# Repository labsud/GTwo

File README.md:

<h1 id="gtwo_shield_for_arduino_due_tinyg_2">GTwo Shield for Arduino DUE &amp; TinyG 2</h1>

<p><a href="https://github.com/synthetos/TinyG">TinyG</a> is a 6 axis motion control system designed by Synthetos for driving CNC, Laser cutters, ans so on. It have been designed to run on Atmel ATxmega192. It&#8217;s a complete system (hard + soft).</p>

<p>Some faeatures : </p>

<ul>
<li>6 axis motion (XYZABC axes)</li>
<li>jerk controlled motion for acceleration planning (3rd order motion planning)</li>
<li>status displays (&#8216;?&#8217; character)</li>
<li>XON/XOFF and RTS/CTS protocol over USB serial</li>
<li>RESTful interface using JSON</li>
</ul>

<p><a href="https://github.com/synthetos/g2">TinyG 2</a> is a TinyG ARM port, also developed by Synthetos, working on Atmel Arm Processors, like the one used on low cost Arduino DUE. That port can be configured for using GRBL shields (Arduino Uno form factor) but unfortunately, pinout is slightly differents, so there&#8217;s no way to have more than 3 motors running. No commands, no emergency stops, spindle or homing&#8230; </p>

<p>GTwo is a shield designed to allow easy use or the port of TinyG with all functionnalities. </p>

<p>That shield can be used :</p>

<ul>
<li>Directly connected to a <a href="https://www.google.fr/search?q=tb6560+red&amp;num=20&amp;safe=off&amp;source=lnms&amp;tbm=isch&amp;sa=X&amp;ved=0ahUKEwinnOrSrarKAhXkpnIKHYe3DXwQ_AUIBygB&amp;biw=917&amp;bih=418">TB 6560 &#8220;Red&#8221;</a>, for a maximum of 4 axis (X,Y,Z,A) and 4 GPIO inputs (I.E. homing X,Y,Z and emergency stop)</li>
<li>Connected thru 6 X 6 pins connectors to discrete drivers like Leadshine, Gekko, etc., allowing up to 6 axis (X,Y,Z,A,B,C).</li>
</ul>

<h4 id="caracteristics">Caracteristics</h4>

<ul>
<li>Mostly passive shield, with all connectors for connecting spindle, PWM Spindle, coolant, homing &amp; Limits, switch for program control, up to 6 axis stepper driver boards</li>
<li>Since DUE is not 5V tolerant, limits inputs are level translated to be used @5V</li>
<li>All other inouts ARE not, and should no be connected to anything else than a 0V. (program control)</li>
</ul>

<h4 id="connections">Connections</h4>

<h5 id="when_using_a_tb6560_power_board_">When using a TB6560 power board :</h5>

That work is the property of Jean-Philippe Civade (jp at civade dot com) and is shared under <a href="licence-CC-By-NC 3.0.txt">Creative Common NonCommercial 3.0</a>

<ul>
<li>JP1 : For connectig to a TB6560 &#8220;Red&#8221; Stepper driver board. A cable must be made with a HE10-26F > DB25F emulating parallel port. If using JP1, don&#8217;t use M1>M6</li>
<li>JP2 : Limits configuration for TB6560. Must be left unequipped if using M1 > M6 connections.</li>
<li>JP4 : Relay config. Must be left unequipped if using M1 > M6 connections.</li>
</ul>

<h5 id="when_using_m1_m6_connections_to_discrete_drivers">When using M1 > M6 connections to discrete drivers</h5>

<ul>
<li>M1 > M6 : Allows to connect up to 6 steppers motors (X/Y/Z/A/B/C). If using M1>M6, don&#8217;t use JP1.</li>
<li>JP3 : Limits inputs. Allow to connect limit and/or homing switches (X-, X+, Y-, Y+, Z-, Z+), emergency stop and optionnaly Hardware interlock. All inputs are 5V tolerant.</li>
<li>JP6 : Stepper power conf </li>
</ul>

<p>M1 to M6 pinout :
* Broche 1 : Step
* Broche 2 : Dir
* Broche 3 : Enable motor (independant enable for each axis)
* Broche 4 : GND
* Broche 5 : Global Enable for all axis
* Broche 6 : VCC (3.3V or 5V depending of JP6) setting</p>

<h5 id="other_connectors_">Other connectors :</h5>

<ul>
<li>JP5 : Spindle &amp; Coolant outputs (3.3V). &#8220;Spindle&#8221; is for Spindle on/off, &#8220;dir&#8221; is for spindle direction (CW/CCW), &#8220;PWM&#8221; is for connecting a PWM spindle, &#8220;PW2&#8221; is an optionnal secondary PWM, &#8220;Cool&#8221; is for connecting cooolant command. </li>
<li>JP7 : Control inputs. Connect swtches for Soft Reset (SR), Feed Hold (Hold), Cycle Start (Run), Emergency Stop (ESTP) or hardware reset (RST)</li>
</ul>

<h5 id="configuration_jumpers_">Configuration Jumpers :</h5>

<p>JP2 : Must be equipped with 4 jumpers allowing to route X- or X+ to Pin 10 of parallel port, Y- or Y+ to pin 11 of parallel port, Z-or Z+ on pin 12 of paralel port, and emergency stop or hardware interlock on pin 13 of parallel port. 
JP4 : Must be equipped with 1 jumper allowing to route motor or coolant to the embedded relay of TB6560 red board.
JP6 : Must be equipped with 1 jumper to route a 3.3V or a 5V to M1 > M6 pin 6.</p>

<h5 id="associated_documents_">Associated Documents :</h5>

<ul>
<li><a href="GTwoShieldSchematics.pdf">Schematics</a></li>
<li><a href="partlist.txt">BOM</a></li>
<li><a href="GTwoShield.zip">ZIP archive for manufacturing</a></li>
<li><a href="imgs/DUE tinyG2 pinout 0.2.pdf">Due Pinout for Tiny G2</a></li>
<li><a href="imgs/GTwoShieldAssembly.pdf">Assembly</a></li>
<li><a href="imgs/GTwoShieldTop.png">Top view</a></li>
<li><a href="imgs/GTwoShieldBottom.png">Bottom view</a></li>
</ul>

<h5 id="example_configuration_">Example configuration :</h5>

<p>This configuration fits to a machine with origin switches at the bottom left ad top Z, for a CNC machine. GTtwo is connected to a TB6560 driver board, and board relay is used to power the spindle. (motor = M3/M5 Gcode). 
TB6560 inputs are Xmin, Ymin, ZMax, Emergency stop. A 3.3V is routed to M1>M6 pin 6.</p>

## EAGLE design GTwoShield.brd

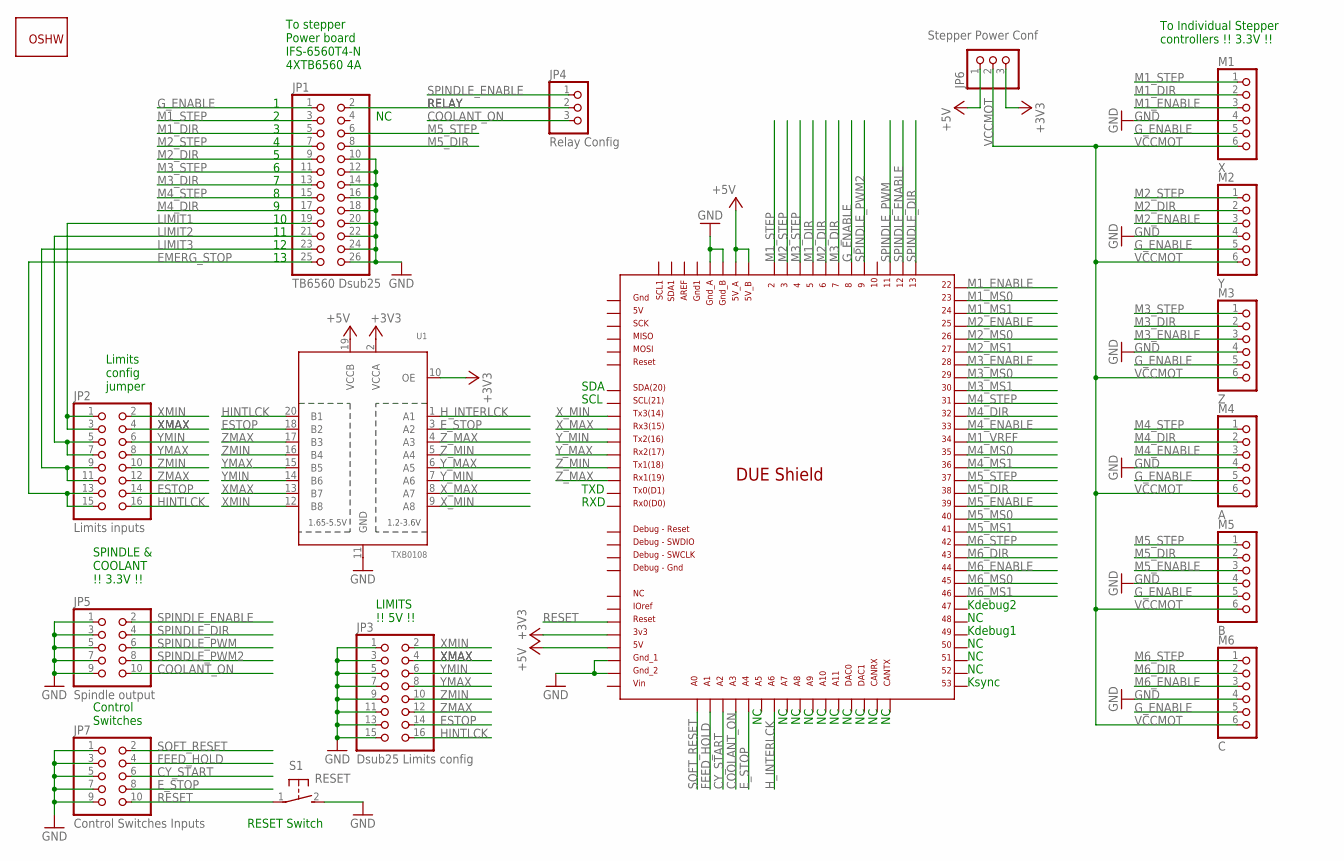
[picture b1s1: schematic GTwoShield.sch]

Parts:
GOLD_ORB_SM1: OSHWLOGO_GOLD_ORB_MED; OSHW1
JP1: TB6560 Dsub25; 2X13
JP2: Limits inputs; 2X08
JP3: Dsub25 Limits config; 2X08
JP4: Relay Config; 1X03
JP5: Spindle output; 2X05
JP6: Stepper Power Conf; 1X03
JP7: Control Switches Inputs; 2X05
M1: X; 1X06
M2: Y; 1X06
M3: Z; 1X06
M4: A; 1X06
M5: B; 1X06
M6: C; 1X06
S1: RESET; B3F-31XX
U1: TXB0108; TSSOP20
U$1: DUE(NORMAL)

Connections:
+3V3: JP6.3, U1.2 (VCCA), U1.10 (OE), U$1.3V3
+5V: JP6.1, U1.19 (VCCB), U$1.5V, U$1.5V_A, U$1.5V_B
COOLANT_ON: JP4.3, JP5.10, U$1.A3
CY_START: JP7.6, U$1.A2
EMERG_STOP: JP1.25, JP2.13, JP2.15
ESTOP: JP2.14, JP3.14, U1.18 (B2)
E_STOP: JP7.8, U1.3 (A2), U$1.A4
FEED_HOLD: JP7.4, U$1.A1
GND: JP1.10, JP1.12, JP1.14, JP1.16, JP1.18, JP1.20, JP1.22, JP1.24, JP1.26, JP3.1, JP3.3, JP3.5, JP3.7, JP3.9, JP3.11, JP3.13, JP3.15, JP5.1, JP5.3, JP5.5, JP5.7, JP5.9, JP7.1, JP7.3, JP7.5, JP7.7, JP7.9, M1.4, M2.4, M3.4, M4.4, M5.4, M6.4, S1.2 (S), U1.11 (GND), U$1.GND_1, U$1.GND_2, U$1.GND_A, U$1.GND_B
G_ENABLE: JP1.1, M1.5, M2.5, M3.5, M4.5, M5.5, M6.5, U$1.8
HINTLCK: JP2.16, JP3.16, U1.20 (B1)
H_INTERLCK: U1.1 (A1), U$1.A6
LIMIT1: JP1.19, JP2.1, JP2.3
LIMIT2: JP1.21, JP2.5, JP2.7
LIMIT3: JP1.23, JP2.9, JP2.11
M1_DIR: JP1.5, M1.2, U$1.5
M1_ENABLE: M1.3, U$1.22
M1_MS0: U$1.23
M1_MS1: U$1.24
M1_STEP: JP1.3, M1.1, U$1.2
M1_VREF: U$1.34
M2_DIR: JP1.9, M2.2, U$1.6
M2_ENABLE: M2.3, U$1.25
M2_MS0: U$1.26
M2_MS1: U$1.27
M2_STEP: JP1.7, M2.1, U$1.3
M3_DIR: JP1.13, M3.2, U$1.7
M3_ENABLE: M3.3, U$1.28
M3_MS0: U$1.29
M3_MS1: U$1.30
M3_STEP: JP1.11, M3.1, U$1.4
M4_DIR: JP1.17, M4.2, U$1.32
M4_ENABLE: M4.3, U$1.33
M4_MS0: U$1.35
M4_MS1: U$1.36
M4_STEP: JP1.15, M4.1, U$1.31
M5_DIR: JP1.8, M5.2, U$1.38
M5_ENABLE: M5.3, U$1.39
M5_MS0: U$1.40
M5_MS1: U$1.41
M5_STEP: JP1.6, M5.1, U$1.37
M6_DIR: M6.2, U$1.43
M6_ENABLE: M6.3, U$1.44
M6_MS0: U$1.45
M6_MS1: U$1.46
M6_STEP: M6.1, U$1.42
RELAY: JP1.2, JP4.2
RESET: JP7.10, S1.1, U$1.RESET
SOFT_RESET: JP7.2, U$1.A0
SPINDLE_DIR: JP5.4, U$1.13
SPINDLE_ENABLE: JP4.1, JP5.2, U$1.12
SPINDLE_PWM: JP5.6, U$1.11
SPINDLE_PWM2: JP5.8, U$1.9
VCCMOT: JP6.2, M1.6, M2.6, M3.6, M4.6, M5.6, M6.6
XMAX: JP2.4, JP3.4, U1.13 (B7)
XMIN: JP2.2, JP3.2, U1.12 (B8)
X_MAX: U1.8 (A7), U$1.RX3
X_MIN: U1.9 (A8), U$1.TX3
YMAX: JP2.8, JP3.8, U1.15 (B5)
YMIN: JP2.6, JP3.6, U1.14 (B6)
Y_MAX: U1.6 (A5), U$1.RX2
Y_MIN: U1.7 (A6), U$1.TX2
ZMAX: JP2.12, JP3.12, U1.17 (B3)
ZMIN: JP2.10, JP3.10, U1.16 (B4)
Z_MAX: U1.4 (A3), U$1.RX1
Z_MIN: U1.5 (A4), U$1.TX1

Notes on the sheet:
Kdebug2
Kdebug1
Ksync
SDA
SCL
TXD
RXD
To stepper Power board IFS-6560T4-N 4XTB6560 4A
Limits config jumper
To Individual Stepper controllers !! 3.3V !!
SPINDLE & COOLANT !! 3.3V !!
Control Switches
RESET Switch
LIMITS !! 5V !!

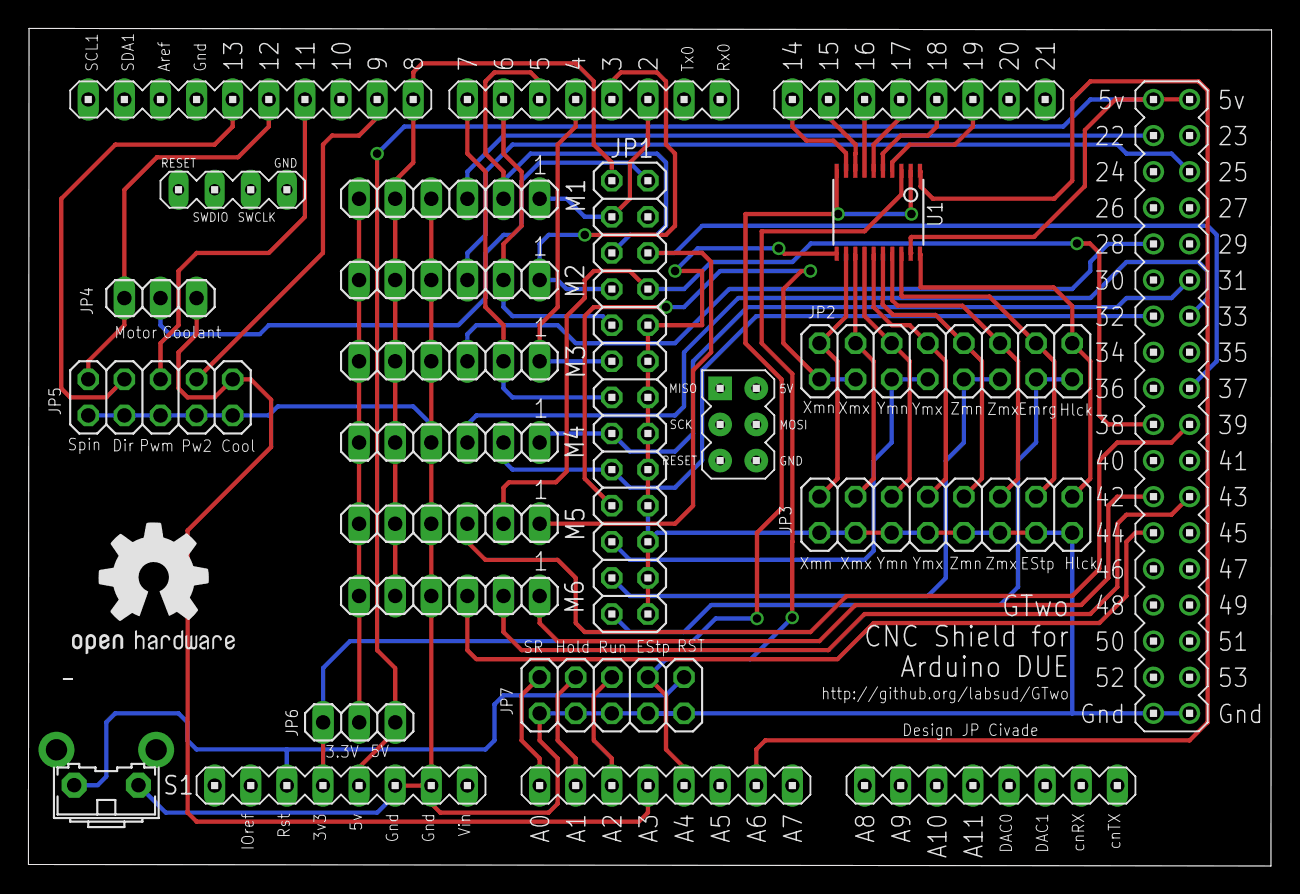
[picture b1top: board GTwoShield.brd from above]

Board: 2 copper layers, 87.4 x 58.9 mm, 17 parts (0 on the bottom side), 53 nets.

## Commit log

2016-01-16 Add licence
